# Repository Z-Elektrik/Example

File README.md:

# Example
 Example KiCad project
 
 Online preview : https://kicanvas.org/?github=https%3A%2F%2Fgithub.com%2FZ-Elektrik%2FExample

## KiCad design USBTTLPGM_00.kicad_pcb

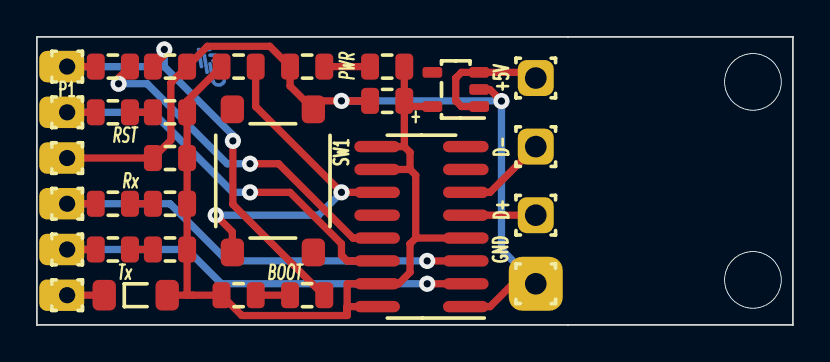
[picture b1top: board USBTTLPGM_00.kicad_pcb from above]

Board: 2 copper layers, 42.0 x 16.0 mm, 29 parts (0 on the bottom side), 17 nets.

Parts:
C1: 4u7/6.3V; CAPCP2012X120N_0805_Case-R
C2: 100n; CAPC2012X85N_0805
CN1: +5V; PAD_THD_R200_200R50H120
CN2: D-; PAD_THD_R200_200R50H120
CN3: D+; PAD_THD_R200_200R50H120
CN4: GND; PAD_THD_R200_200R50H120
D1: LL4148; DIOMELF3414N_DO213AC_MiniMELF
IC1: LR6207; SOT95P280X145-5N_SOT23-5__12345
IC2: CH340C; SOP127P700X200-16N_SOP-16
LD1, LD2: KP-2012MGC-Green; LEDC2012X100_0805_Green
LD3: KP-2012MGC-Green; LEDC2012X100_0805_Blue
LD4: KP-2012SYCK-Yellow; LEDC2012X100_0805_Yellow
LD5: KP-2012SURCK-Red; LEDC2012X100_0805_Red
P1: Boot; PAD_THD_R150_150R37H90
P2: RST; PAD_THD_R150_150R37H90
P3: GND; PAD_THD_R150_150R37H90
P4: Rx; PAD_THD_R150_150R37H90
P5: Tx; PAD_THD_R150_150R37H90
P6: +3Vout; PAD_THD_R150_150R37H90
R1: 10k 5%; RESC2012X50N_0805
R2, R3, R8, R9, R10: 2k2 5%; RESC2012X50N_0805
R4, R5: 0R; RESC2012X50N_0805
SW1: B3S-1000; SW_PUSH_450P600X600H430-4N_Omron

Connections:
GND: C1.2, C2.1, CN4.1, IC1.2 (GND), IC2.1 (GND), P3.1, R5.1, R10.1, SW1.4
unnamed: C1.1, C2.2, D1.2 (A), IC1.5 (OUT), IC2.4 (V3), IC2.9 (~CTS), IC2.10 (~DSR), IC2.15 (RS232), IC2.16 (VCC), LD5.A, R1.2, R2.2, R3.2, R8.2, R9.2
unnamed: D1.1 (C), P6.1
unnamed: CN1.1, IC1.1 (VIN), IC1.3 (EN)
unnamed: IC2.3 (RXD), LD4.C, P4.1
unnamed: IC2.2 (TXD), LD3.C, P5.1
unnamed: CN2.1, IC2.6 (USBDM)
unnamed: CN3.1, IC2.5 (USBDP)
unnamed: IC2.13 (~DTR), R4.1
unnamed: IC2.11 (~RI), R1.1, SW1.1
unnamed: IC2.14 (~RTS), LD1.C, P2.1
unnamed: LD1.A, R2.1
unnamed: LD2.A, R3.1
unnamed: LD2.C, P1.1, R4.2, R5.2
unnamed: LD3.A, R8.1
unnamed: LD4.A, R9.1
unnamed: LD5.C, R10.2

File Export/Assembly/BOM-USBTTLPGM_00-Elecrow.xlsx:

Item | Reference | QTY | Value | LibPart | Package | Datasheet | DNP | Comment | MFG | Manufacturer Part number | OC_DIGIKEY | OC_DISTRELEC | OC_FARNELL | LCSC Part# | OC_MOUSER | OC_RS | OC_SOS | OC_TME | Technology | Z-SYSCODE
1 | C1 | 1 | 4u7/6.3V | Capacitor_Tantal_0805_6.3V_10perc_AVX:4u7, SMD 0805, 6.3V, 10%, AVX | SMD_Capacitor_Polarised_Generic:CAPCP2012X120N_0805_Case-R | https://www.mouser.sk/datasheet/2/40/TAJ_LOW_PROFILE-932651.pdf |  |  | AVX | TAJR475K006RNJ | 478-3272-1-ND |  |  | C308815 |  | 135-5398 |  | TAJR475K006RNJ | SMD | 11588
2 | C2 | 1 | 100n | Capacitor_Ceramic_0805_50V_X7R_Generic:100n, SMD 0805, 50V, X7R | SMD_Capacitor_NonPolarised_Generic:CAPC2012X85N_0805 |  |  |  | Generic | CC0805KRX7R9BB104 |  |  |  | C49678 |  |  |  |  | SMD | 794
3 | D1 | 1 | LL4148 | Diode_ONSemi:LL4148 | SMD_Semiconductor_Generic:DIOMELF3414N_DO213AC_MiniMELF | https://www.tme.eu/Document/719e3c29769cb8dee605f959a3db8a4a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 |  |  | ON Semiconductor | LL4148 | LL4148FSCT-ND | 302-30-889 | 2101203 | C84135 | 512-LL4148 | 670-8826 | T372589 | LL4148-FAI | SMD | 1138
4 | IC1 | 1 | LR6207 | IC_Power_Lory:LR6207A-T33 | SMD_Semiconductor_Generic:SOT95P280X145-5N_SOT23-5__12345 | https://www.mouser.sk/datasheet/2/268/21813F-892413.pdf |  | Alt: TC-1017-3.3 | Lory Semiconductor | LR6207A-T33 |  |  |  | C5260329 |  |  |  |  | SMD
5 | IC2 | 1 | CH340C | IC_Interface_Nanjing:CH340C | SMD_IC_Generic:SOP127P700X200-16N_SOP-16 | https://datasheet.lcsc.com/lcsc/2304140030_WCH-Jiangsu-Qin-H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 |  |  | Nanjing Qinheng Microelectronics | CH340C |  |  |  | C84681 |  |  |  |  | SMD
6 | LD1, LD2 | 2 | KP-2012MGC-Green | Opto_Kingbright:KP-2012SMGC-Green | SMD_LED_Generic:LEDC2012X100_0805_Green | https://cdn.sos.sk/productdata/7f/b3/9360e0f5/kp-2012-mgc.pdf |  | RST | Kingbright | KP-2012MGC |  |  | 8529906 | C598275 |  |  | 72204 | KP-2012MGC | SMD | 10691
7 | LD3 | 1 | KP-2012MGC-Green | Opto_Kingbright:KP-2012QBC-D-Blue | SMD_LED_Generic:LEDC2012X100_0805_Blue | https://cdn.sos.sk/productdata/5e/9e/87fe918b/kp-2012-qbc-d.pdf |  | Tx | Kingbright | KP-2012QBC-D |  |  | 2846594 | C598277 |  |  | 80975 | KP-2012QBC-D | SMD | 10690
8 | LD4 | 1 | KP-2012SYCK-Yellow | Opto_Kingbright:KP-2012SYCK-Yellow | SMD_LED_Generic:LEDC2012X100_0805_Yellow | https://cdn.sos.sk/productdata/22/b7/a74d10b5/kp-2012-syck.pdf |  | Rx | Kingbright | KP-2012SYCK |  |  | 1318246 | C598287 |  |  | 59713 | KP-2012SYCK | SMD | 491
9 | LD5 | 1 | KP-2012SURCK-Red | Opto_Kingbright:KP-2012SURCK-Red | SMD_LED_Generic:LEDC2012X100_0805_Red | https://datasheet.lcsc.com/lcsc/2008121135_Kingbright-KP-201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 |  | PWR | Kingbright | KP-2012SURCK |  |  | 1318245 | C598285 |  |  | 120878 | KP-2012SURCK | SMD | 10689
10 | R1 | 1 | 10k 5% | Resistor_SMD_0805_0.125W_5perc_100ppm_Yageo:10k, SMD 0805, 0.125W, 5%, 100ppm, 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 | SMD_Resistor_Generic:RESC2012X50N_0805 |  |  |  | Yageo | RC0805JR-0710KL | 311-10KARCT-ND | 302-14-026 | 9234136 | C100047 | 603-RC0805JR-0710KL | 199-5760 |  | RC0805JR-0710K | SMD | 1217
11 | R2, R3, R8, R9, R10 | 5 | 2k2 5% | Resistor_SMD_0805_0.125W_5perc_100ppm_Yageo:2k2, SMD 0805, 0.125W, 5%, 100ppm, 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 | SMD_Resistor_Generic:RESC2012X50N_0805 | https://www.farnell.com/datasheets/3795017.pdf |  |  | Yageo | RC0805JR-072K2L | 311-2.2KARCT-ND |  | 9234055 | C114237 | 603-RC0805JR-072K2L | 199-5764 |  | RC0805JR-072K2 | SMD
12 | R4, R5 | 2 | 0R | Resistor_SMD_0805_0.125W_5perc_100ppm_Yageo:0R Jumper, SMD 0805, 0.125W, 5%, 20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 | SMD_Resistor_Generic:RESC2012X50N_0805 | https://www.yageo.com/upload/media/product/productsearch/dat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 |  |  | Yageo | AC0805JR-070RL | YAG3755CT-ND | 302-14-027 | 3495331 | C144539 | 603-AC0805JR-070RL | 197-8210 |  | AC0805JR-070RL | SMD | 331
13 | SW1 | 1 | B3S-1000 | Switch_Omron:B3S-1000 | SMD_Switch_Omron:SW_PUSH_450P600X600H430-4N_Omron | https://www.tme.eu/Document/1a744fb026617d7259891fb0eea6ebae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 |  |  | Omron | B3S-1000(P) | SW415-ND | 135-59-087 | 177807 | C180420 | 653-B3S-1000 | 183-701 | 6656 | B3S-1000P | SMD | 905
